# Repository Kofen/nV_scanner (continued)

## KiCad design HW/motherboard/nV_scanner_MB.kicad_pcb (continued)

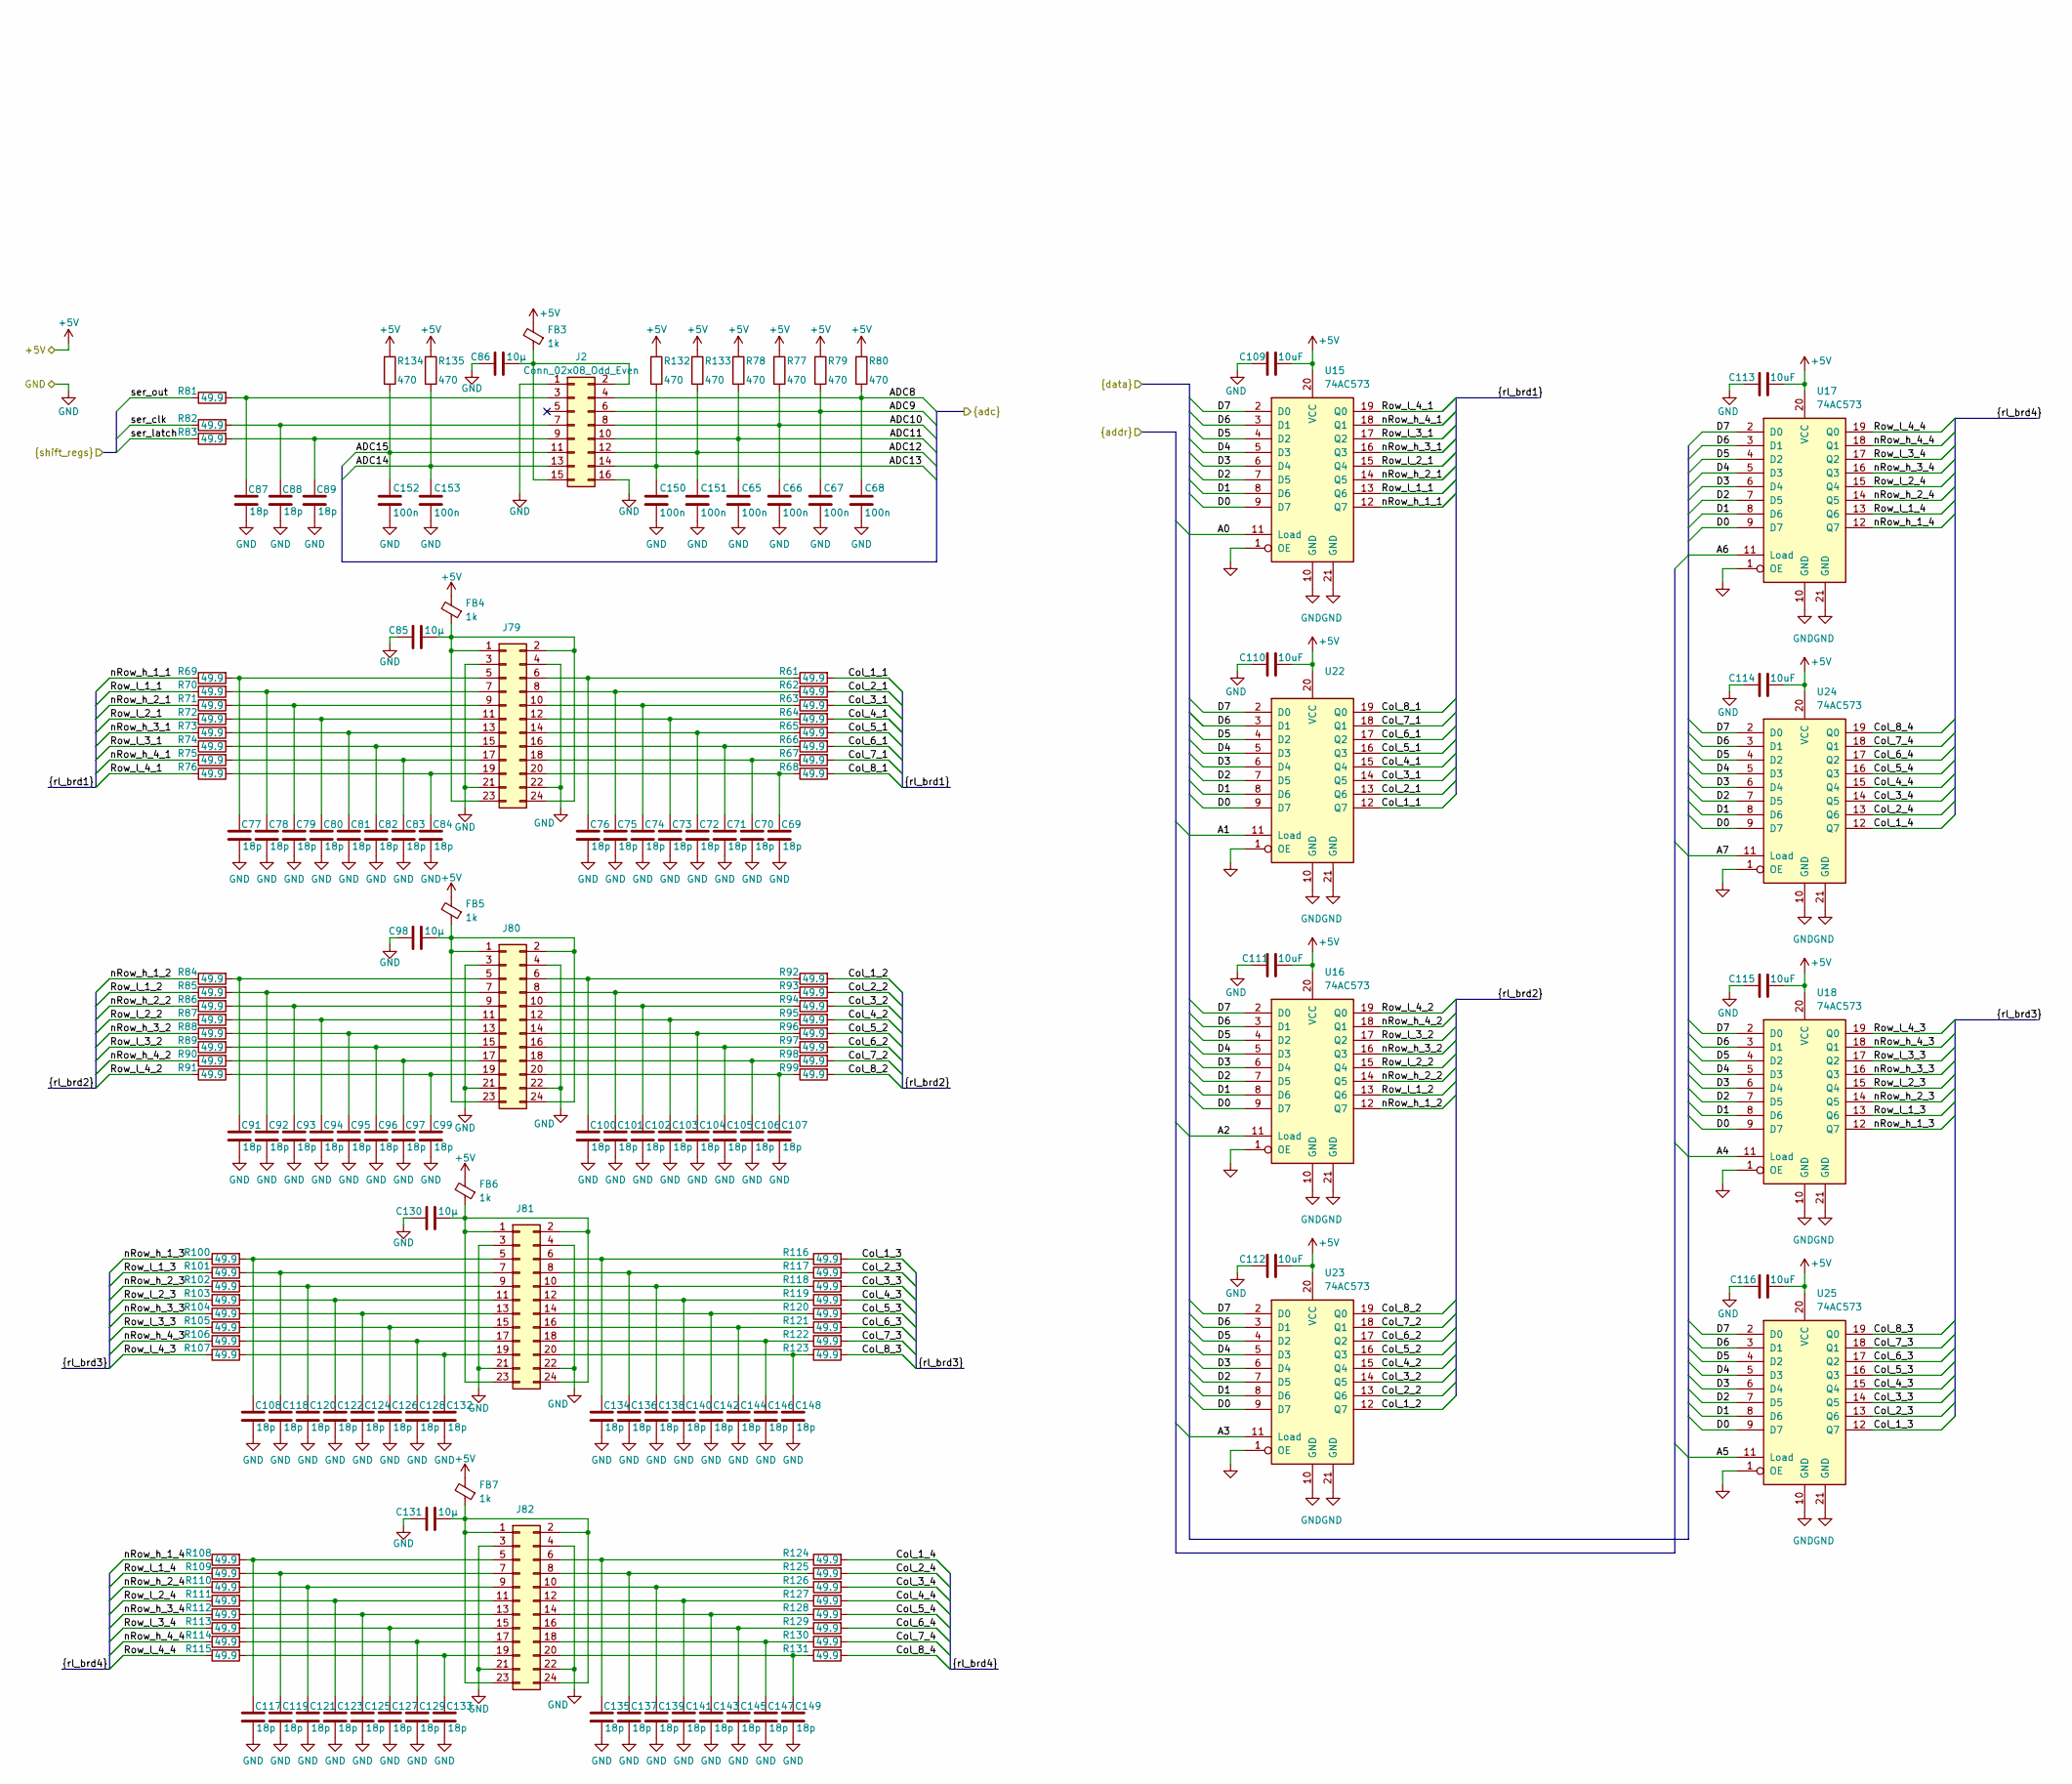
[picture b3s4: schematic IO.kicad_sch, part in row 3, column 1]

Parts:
C65, C66, C67, C68, C150, C151, C152, C153: 100n; C_0402_1005Metric; JLCPCB C1525
C69, C70, C71, C72, C73, C74, C75, C76, C77, C78, C79, C80, C81, C82, C83, C84, C87, C88, C89, C91, C92, C93, C94, C95, C96, C97, C99, C100, C101, C102, C103, C104, C105, C106, C107, C108, C117, C118, C119, C120, C121, C122, C123, C124, C125, C126, C127, C128, C129, C132, C133, C134, C135, C136, C137, C138, C139, C140, C141, C142, C143, C144, C145, C146, C147, C148, C149: 18p; C_0402_1005Metric; JLCPCB C1549
C85, C86, C98, C130, C131: 10µ; C_0402_1005Metric; JLCPCB C15525
C109, C110, C111, C112, C113, C114, C115, C116: 10uF; C_0603_1608Metric
FB3, FB4, FB5, FB6, FB7: 1k; L_0805_2012Metric; JLCPCB C710395
J2: Conn_02x08_Odd_Even; PinHeader_2x08_P2.54mm_Vertical
J79, J80, J81, J82: Conn_02x12_Odd_Even; PinHeader_2x12_P2.54mm_Vertical
R61, R62, R63, R64, R65, R66, R67, R68, R69, R70, R71, R72, R73, R74, R75, R76, R81, R82, R83, R84, R85, R86, R87, R88, R89, R90, R91, R92, R93, R94, R95, R96, R97, R98, R99, R100, R101, R102, R103, R104, R105, R106, R107, R108, R109, R110, R111, R112, R113, R114, R115, R116, R117, R118, R119, R120, R121, R122, R123, R124, R125, R126, R127, R128, R129, R130, R131: 49.9; R_0402_1005Metric
R77, R78, R79, R80, R132, R133, R134, R135: 470; R_0603_1608Metric
U15, U16, U17, U18, U22, U23, U24, U25: 74AC573; DHVQFN-20-1EP_2.5x4.5mm_P0.5mm_EP1x3mm

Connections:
+5V: C109.2, C110.2, C111.2, C112.2, C113.2, C114.2, C115.2, C116.2, FB3.2, FB4.2, FB5.2, FB6.2, FB7.2, R77.2, R78.2, R79.2, R80.2, R132.2, R133.2, R134.2, R135.2, U15.20 (VCC), U16.20 (VCC), U17.20 (VCC), U18.20 (VCC), U22.20 (VCC), U23.20 (VCC), U24.20 (VCC), U25.20 (VCC); also elsewhere on the board
/IO/A0: U15.11 (Load); also elsewhere on the board
/IO/A1: U22.11 (Load); also elsewhere on the board
/IO/A2: U16.11 (Load); also elsewhere on the board
/IO/A3: U23.11 (Load); also elsewhere on the board
/IO/A4: U18.11 (Load); also elsewhere on the board
/IO/A5: U25.11 (Load); also elsewhere on the board
/IO/A6: U17.11 (Load); also elsewhere on the board
/IO/A7: U24.11 (Load); also elsewhere on the board
/IO/ADC8: C68.2, J2.4, R80.1; also elsewhere on the board
/IO/ADC9: C67.2, J2.6, R79.1; also elsewhere on the board
/IO/ADC10: C66.2, J2.8, R77.1; also elsewhere on the board
/IO/ADC11: C65.2, J2.10, R78.1; also elsewhere on the board
/IO/ADC12: C151.2, J2.12, R133.1; also elsewhere on the board
/IO/ADC13: C150.2, J2.14, R132.1; also elsewhere on the board
/IO/ADC14: C153.2, J2.13, R135.1; also elsewhere on the board
/IO/ADC15: C152.2, J2.11, R134.1; also elsewhere on the board
/IO/Col_1_1: R61.2, U22.12 (Q7)
/IO/Col_1_2: R92.2, U23.12 (Q7)
/IO/Col_1_3: R116.2, U25.12 (Q7)
/IO/Col_1_4: R124.2, U24.12 (Q7)
/IO/Col_2_1: R62.2, U22.13 (Q6)
/IO/Col_2_2: R93.2, U23.13 (Q6)
/IO/Col_2_3: R117.2, U25.13 (Q6)
/IO/Col_2_4: R125.2, U24.13 (Q6)
/IO/Col_3_1: R63.2, U22.14 (Q5)
/IO/Col_3_2: R94.2, U23.14 (Q5)
/IO/Col_3_3: R118.2, U25.14 (Q5)
/IO/Col_3_4: R126.2, U24.14 (Q5)
/IO/Col_4_1: R64.2, U22.15 (Q4)
/IO/Col_4_2: R95.2, U23.15 (Q4)
/IO/Col_4_3: R119.2, U25.15 (Q4)
/IO/Col_4_4: R127.2, U24.15 (Q4)
/IO/Col_5_1: R65.2, U22.16 (Q3)
/IO/Col_5_2: R96.2, U23.16 (Q3)
/IO/Col_5_3: R120.2, U25.16 (Q3)
/IO/Col_5_4: R128.2, U24.16 (Q3)
/IO/Col_6_1: R66.2, U22.17 (Q2)
/IO/Col_6_2: R97.2, U23.17 (Q2)
/IO/Col_6_3: R121.2, U25.17 (Q2)
/IO/Col_6_4: R129.2, U24.17 (Q2)
/IO/Col_7_1: R67.2, U22.18 (Q1)
/IO/Col_7_2: R98.2, U23.18 (Q1)
/IO/Col_7_3: R122.2, U25.18 (Q1)
/IO/Col_7_4: R130.2, U24.18 (Q1)
/IO/Col_8_1: R68.2, U22.19 (Q0)
/IO/Col_8_2: R99.2, U23.19 (Q0)
/IO/Col_8_3: R123.2, U25.19 (Q0)
/IO/Col_8_4: R131.2, U24.19 (Q0)
/IO/D0: U15.9 (D7), U16.9 (D7), U17.9 (D7), U18.9 (D7), U22.9 (D7), U23.9 (D7), U24.9 (D7), U25.9 (D7); also elsewhere on the board
/IO/D1: U15.8 (D6), U16.8 (D6), U17.8 (D6), U18.8 (D6), U22.8 (D6), U23.8 (D6), U24.8 (D6), U25.8 (D6); also elsewhere on the board
/IO/D2: U15.7 (D5), U16.7 (D5), U17.7 (D5), U18.7 (D5), U22.7 (D5), U23.7 (D5), U24.7 (D5), U25.7 (D5); also elsewhere on the board
/IO/D3: U15.6 (D4), U16.6 (D4), U17.6 (D4), U18.6 (D4), U22.6 (D4), U23.6 (D4), U24.6 (D4), U25.6 (D4); also elsewhere on the board
/IO/D4: U15.5 (D3), U16.5 (D3), U17.5 (D3), U18.5 (D3), U22.5 (D3), U23.5 (D3), U24.5 (D3), U25.5 (D3); also elsewhere on the board
/IO/D5: U15.4 (D2), U16.4 (D2), U17.4 (D2), U18.4 (D2), U22.4 (D2), U23.4 (D2), U24.4 (D2), U25.4 (D2); also elsewhere on the board
/IO/D6: U15.3 (D1), U16.3 (D1), U17.3 (D1), U18.3 (D1), U22.3 (D1), U23.3 (D1), U24.3 (D1), U25.3 (D1); also elsewhere on the board
/IO/D7: U15.2 (D0), U16.2 (D0), U17.2 (D0), U18.2 (D0), U22.2 (D0), U23.2 (D0), U24.2 (D0), U25.2 (D0); also elsewhere on the board
/IO/Row_l_1_1: R70.1, U15.13 (Q6)
/IO/Row_l_1_2: R85.1, U16.13 (Q6)
/IO/Row_l_1_3: R101.1, U18.13 (Q6)
/IO/Row_l_1_4: R109.1, U17.13 (Q6)
/IO/Row_l_2_1: R72.1, U15.15 (Q4)
/IO/Row_l_2_2: R87.1, U16.15 (Q4)
/IO/Row_l_2_3: R103.1, U18.15 (Q4)
/IO/Row_l_2_4: R111.1, U17.15 (Q4)
/IO/Row_l_3_1: R74.1, U15.17 (Q2)
/IO/Row_l_3_2: R89.1, U16.17 (Q2)
/IO/Row_l_3_3: R105.1, U18.17 (Q2)
/IO/Row_l_3_4: R113.1, U17.17 (Q2)
/IO/Row_l_4_1: R76.1, U15.19 (Q0)
/IO/Row_l_4_2: R91.1, U16.19 (Q0)
/IO/Row_l_4_3: R107.1, U18.19 (Q0)
/IO/Row_l_4_4: R115.1, U17.19 (Q0)
/IO/nRow_h_1_1: R69.1, U15.12 (Q7)
/IO/nRow_h_1_2: R84.1, U16.12 (Q7)
/IO/nRow_h_1_3: R100.1, U18.12 (Q7)
/IO/nRow_h_1_4: R108.1, U17.12 (Q7)
/IO/nRow_h_2_1: R71.1, U15.14 (Q5)
/IO/nRow_h_2_2: R86.1, U16.14 (Q5)
/IO/nRow_h_2_3: R102.1, U18.14 (Q5)
/IO/nRow_h_2_4: R110.1, U17.14 (Q5)
/IO/nRow_h_3_1: R73.1, U15.16 (Q3)
/IO/nRow_h_3_2: R88.1, U16.16 (Q3)
/IO/nRow_h_3_3: R104.1, U18.16 (Q3)
/IO/nRow_h_3_4: R112.1, U17.16 (Q3)
/IO/nRow_h_4_1: R75.1, U15.18 (Q1)
/IO/nRow_h_4_2: R90.1, U16.18 (Q1)
/IO/nRow_h_4_3: R106.1, U18.18 (Q1)
/IO/nRow_h_4_4: R114.1, U17.18 (Q1)
/IO/ser_clk: R82.1; also elsewhere on the board
/IO/ser_latch: R83.1; also elsewhere on the board
/IO/ser_out: R81.1; also elsewhere on the board
GND: C65.1, C66.1, C67.1, C68.1, C69.2, C70.2, C71.2, C72.2, C73.2, C74.2, C75.2, C76.2, C77.2, C78.2, C79.2, C80.2, C81.2, C82.2, C83.2, C84.2, C85.2, C86.2, C87.2, C88.2, C89.2, C91.2, C92.2, C93.2, C94.2, C95.2, C96.2, C97.2, C98.2, C99.2, C100.2, C101.2, C102.2, C103.2, C104.2, C105.2, C106.2, C107.2, C108.2, C109.1, C110.1, C111.1, C112.1, C113.1, C114.1, C115.1, C116.1, C117.2, C118.2, C119.2, C120.2, C121.2, C122.2, C123.2, C124.2, C125.2, C126.2, C127.2, C128.2, C129.2, C130.2, C131.2, C132.2, C133.2, C134.2, C135.2, C136.2, C137.2, C138.2, C139.2, C140.2, C141.2, C142.2, C143.2, C144.2, C145.2, C146.2, C147.2, C148.2, C149.2, C150.1, C151.1, C152.1, C153.1, J2.1, J2.16, J79.3, J79.4, J79.21, J79.22, J80.3, J80.4, J80.21, J80.22, J81.3, J81.4, J81.21, J81.22, J82.3, J82.4, J82.21, J82.22, U15.1 (OE), U15.10 (GND), U15.21 (GND), U16.1 (OE), U16.10 (GND), U16.21 (GND), U17.1 (OE), U17.10 (GND), U17.21 (GND), U18.1 (OE), U18.10 (GND), U18.21 (GND), U22.1 (OE), U22.10 (GND), U22.21 (GND), U23.1 (OE), U23.10 (GND), U23.21 (GND), U24.1 (OE), U24.10 (GND), U24.21 (GND), U25.1 (OE), U25.10 (GND), U25.21 (GND); also elsewhere on the board
unnamed: C87.1, J2.3, R81.2
unnamed: C88.1, J2.7, R82.2
unnamed: C89.1, J2.9, R83.2
unnamed: C86.1, FB3.1, J2.2, J2.15
unnamed: C85.1, FB4.1, J79.1, J79.2, J79.23, J79.24
unnamed: C77.1, J79.5, R69.2
unnamed: C76.1, J79.6, R61.1
unnamed: C78.1, J79.7, R70.2
unnamed: C75.1, J79.8, R62.1
unnamed: C79.1, J79.9, R71.2
unnamed: C74.1, J79.10, R63.1
unnamed: C80.1, J79.11, R72.2
unnamed: C73.1, J79.12, R64.1
unnamed: C81.1, J79.13, R73.2
unnamed: C72.1, J79.14, R65.1
unnamed: C82.1, J79.15, R74.2
unnamed: C71.1, J79.16, R66.1
unnamed: C83.1, J79.17, R75.2
unnamed: C70.1, J79.18, R67.1
unnamed: C84.1, J79.19, R76.2
unnamed: C69.1, J79.20, R68.1
unnamed: C98.1, FB5.1, J80.1, J80.2, J80.23, J80.24
unnamed: C91.1, J80.5, R84.2
unnamed: C100.1, J80.6, R92.1
unnamed: C92.1, J80.7, R85.2
unnamed: C101.1, J80.8, R93.1
unnamed: C93.1, J80.9, R86.2
unnamed: C102.1, J80.10, R94.1
unnamed: C94.1, J80.11, R87.2
unnamed: C103.1, J80.12, R95.1
unnamed: C95.1, J80.13, R88.2
unnamed: C104.1, J80.14, R96.1
unnamed: C96.1, J80.15, R89.2
unnamed: C105.1, J80.16, R97.1
unnamed: C97.1, J80.17, R90.2
unnamed: C106.1, J80.18, R98.1
unnamed: C99.1, J80.19, R91.2
unnamed: C107.1, J80.20, R99.1
unnamed: C130.1, FB6.1, J81.1, J81.2, J81.23, J81.24
unnamed: C108.1, J81.5, R100.2
unnamed: C134.1, J81.6, R116.1
unnamed: C118.1, J81.7, R101.2
unnamed: C136.1, J81.8, R117.1
unnamed: C120.1, J81.9, R102.2
unnamed: C138.1, J81.10, R118.1
unnamed: C122.1, J81.11, R103.2
unnamed: C140.1, J81.12, R119.1
unnamed: C124.1, J81.13, R104.2
unnamed: C142.1, J81.14, R120.1
unnamed: C126.1, J81.15, R105.2
unnamed: C144.1, J81.16, R121.1
unnamed: C128.1, J81.17, R106.2
unnamed: C146.1, J81.18, R122.1
unnamed: C132.1, J81.19, R107.2
unnamed: C148.1, J81.20, R123.1
unnamed: C131.1, FB7.1, J82.1, J82.2, J82.23, J82.24
unnamed: C117.1, J82.5, R108.2
unnamed: C135.1, J82.6, R124.1
unnamed: C119.1, J82.7, R109.2
unnamed: C137.1, J82.8, R125.1
unnamed: C121.1, J82.9, R110.2
unnamed: C139.1, J82.10, R126.1
unnamed: C123.1, J82.11, R111.2
unnamed: C141.1, J82.12, R127.1
unnamed: C125.1, J82.13, R112.2
unnamed: C143.1, J82.14, R128.1
unnamed: C127.1, J82.15, R113.2
unnamed: C145.1, J82.16, R129.1
unnamed: C129.1, J82.17, R114.2
unnamed: C147.1, J82.18, R130.1
unnamed: C133.1, J82.19, R115.2
unnamed: C149.1, J82.20, R131.1

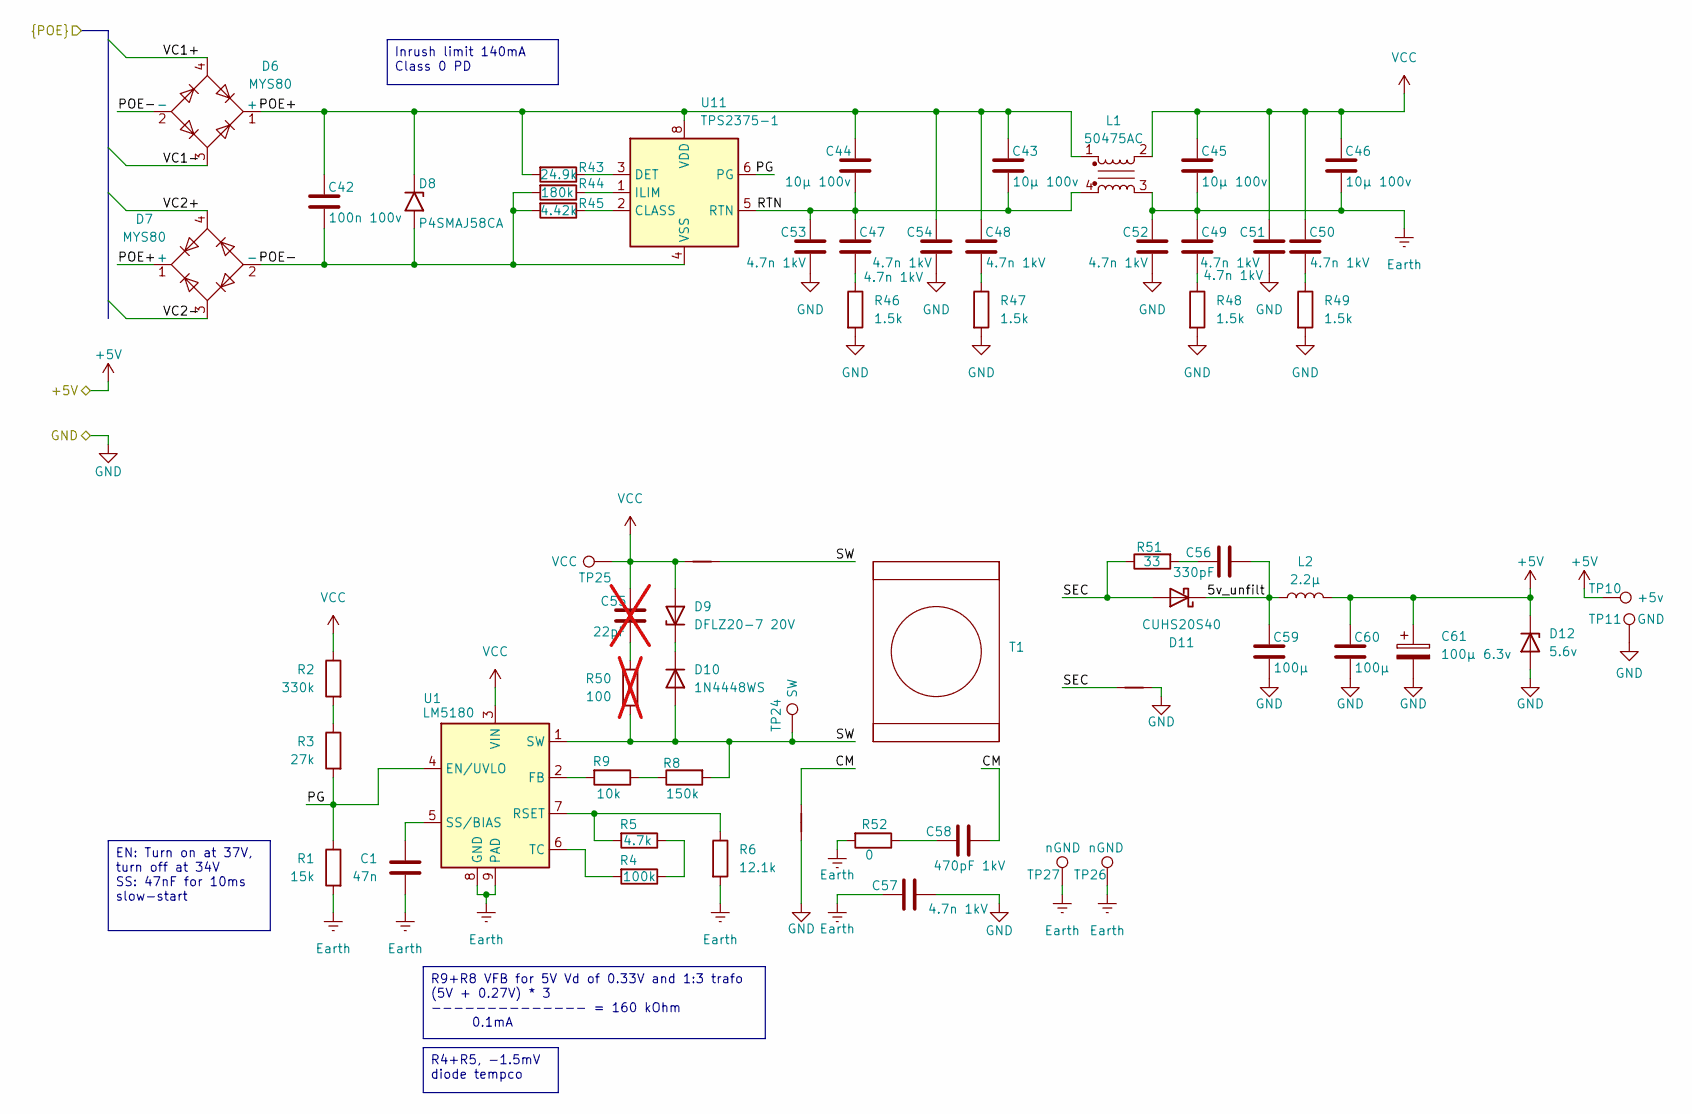
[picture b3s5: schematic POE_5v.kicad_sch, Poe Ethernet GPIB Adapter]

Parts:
C1: 47n; C_0402_1005Metric; JLCPCB C82219
C42: 100n 100v; C_0603_1608Metric; JLCPCB C15725
C43, C44, C45, C46: 10µ 100v; C_1210_3225Metric; JLCPCB C5156756
C47, C48, C49, C50, C51, C52, C53, C54, C57: 4.7n 1kV; C_0805_2012Metric; JLCPCB C565695
C55: 22pF; C_0603_1608Metric; not fitted
C56: 330pF; C_0603_1608Metric; JLCPCB C458879
C58: 470pF 1kV; C_0805_2012Metric; JLCPCB C20416464
C59, C60: 100µ; C_1206_3216Metric; JLCPCB CL31A107MQHNNNE
C61: 100µ 6.3v; CP_Elec_5x5.3; JLCPCB C5530352
D6, D7: MYS80; Diode_Bridge_Diotec_MicroDil_3.0x3.0x1.8mm; JLCPCB C3589669
D8: P4SMAJ58CA; D_SMA; JLCPCB C268635
D9: DFLZ20-7 20V; D_PowerDI-123; JLCPCB C177024
D10: 1N4448WS; D_SOD-323; JLCPCB C8602
D11: CUHS20S40; D_TUMD2; JLCPCB C3758140
D12: 5.6v; D_SOD-123F; JLCPCB C2119
L1: 50475AC; muRata_5000A
L2: 2.2µ; L_Taiyo-Yuden_NR-50xx
NT1, NT2: NetTie_2; NetTie-2_SMD_Pad0.5mm
NT3: NetTie_2; NetTie-2_SMD_Pad0.8mm
R1: 15k; R_0402_1005Metric
R2: 330k; R_0805_2012Metric
R3: 27k; R_0402_1005Metric
R4: 100k; R_0402_1005Metric
R5: 4.7k; R_0402_1005Metric
R6: 12.1k; R_0402_1005Metric
R8: 150k; R_0805_2012Metric
R9: 10k; R_0402_1005Metric
R43: 24.9k; R_0402_1005Metric
R44: 180k; R_0402_1005Metric
R45: 4.42k; R_0402_1005Metric
R46, R47, R48, R49: 1.5k; R_0603_1608Metric
R50: 100; R_0603_1608Metric; not fitted
R51: 33; R_0603_1608Metric
R52: 0; R_0603_1608Metric
T1: ER14_planar_4_to_1_48v_in_5v_out_5w
TP10: +5v; TestPoint_Pad_D1.0mm
TP11: GND; TestPoint_Pad_D1.0mm
TP24: SW; TestPoint_Pad_D1.0mm
TP25: VCC; TestPoint_Pad_D1.0mm
TP26, TP27: nGND; TestPoint_Pad_D1.0mm
U1: LM5180; WSON-8-1EP_4x4mm_P0.8mm_EP1.98x3mm; JLCPCB C2868878
U11: TPS2375-1; TSSOP-8_4.4x3mm_P0.65mm; JLCPCB C2859774

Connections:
+5V: C60.1, C61.1, D12.1 (K), L2.2, TP10.1; also elsewhere on the board
/Ethernet_interface/VC1+: D6.4; also elsewhere on the board
/Ethernet_interface/VC1-: D6.3; also elsewhere on the board
/Ethernet_interface/VC2+: D7.4; also elsewhere on the board
/Ethernet_interface/VC2-: D7.3; also elsewhere on the board
/POE_5v/5v_unfilt: C56.2, C59.1, D11.1 (K), L2.1
/POE_5v/CM: C58.1, NT2.2
/POE_5v/PG: R1.1, R3.2, U1.4 (EN/UVLO), U11.6 (PG)
/POE_5v/POE+: C42.1, C43.1, C44.1, C48.1, C54.1, D6.1 (+), D7.1 (+), D8.1 (A1), L1.1, R43.2, U11.8 (VDD)
/POE_5v/POE-: C42.2, D6.2 (-), D7.2 (-), D8.2 (A2), R44.2, R45.2, U11.4 (VSS)
/POE_5v/RTN: C43.2, C44.2, C47.1, C53.1, L1.4, U11.5 (RTN)
/POE_5v/SEC: D11.2 (A), NT3.1, R51.1
/POE_5v/SW: D10.2 (A), NT1.2, R8.2, R50.2, TP24.1, U1.1 (SW)
Earth: C1.2, C45.2, C46.2, C49.1, C52.1, C57.2, L1.3, R1.2, R6.2, R52.2, TP26.1, TP27.1, U1.8 (GND), U1.9 (PAD)
GND: C51.2, C52.2, C53.2, C54.2, C57.1, C59.2, C60.2, C61.2, D12.2 (A), NT2.1, NT3.2, R46.2, R47.2, R48.2, R49.2, TP11.1; also elsewhere on the board
unnamed: C47.2, R46.1
unnamed: C48.2, R47.1
unnamed: C49.2, R48.1
unnamed: C50.2, R49.1
unnamed: C55.2, R50.1
unnamed: C56.1, R51.2
unnamed: C58.2, R52.1
unnamed: D9.1 (K), D10.1 (K)
unnamed: R2.2, R3.1
unnamed: R4.1, R5.1
unnamed: R8.1, R9.1
unnamed: R9.2, U1.2 (FB)
unnamed: R5.2, R6.1, U1.7 (RSET)
unnamed: C1.1, U1.5 (SS/BIAS)
unnamed: R4.2, U1.6 (TC)
unnamed: R45.1, U11.2 (CLASS)
unnamed: R43.1, U11.3 (DET)
unnamed: R44.1, U11.1 (ILIM)
VCC: C45.1, C46.1, C50.1, C51.1, C55.1, D9.2 (A), L1.2, NT1.1, R2.1, TP25.1, U1.3 (VIN)

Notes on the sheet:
R9+R8 VFB for 5V Vd of 0.33V and 1:3 trafo (5V + 0.27V) * 3 -------------- = 160 kOhm 0.1mA
R4+R5, -1.5mV diode tempco
EN: Turn on at 37V, turn off at 34V SS: 47nF for 10ms slow-start
Inrush limit 140mA Class 0 PD

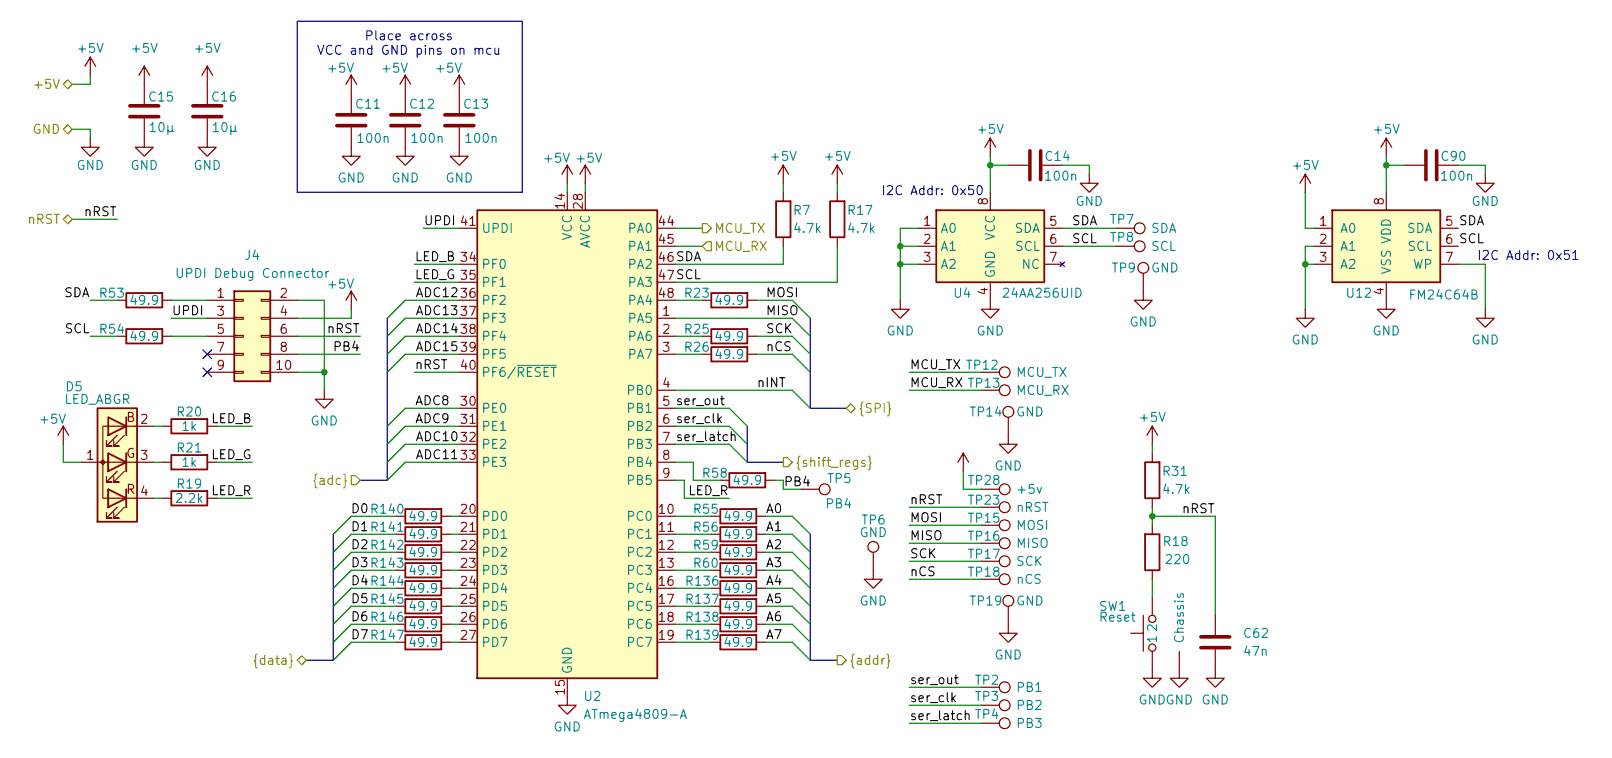
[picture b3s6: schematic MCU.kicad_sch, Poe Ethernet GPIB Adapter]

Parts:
C11, C12, C13, C14, C90: 100n; C_0402_1005Metric; JLCPCB C1525
C15, C16: 10µ; C_0402_1005Metric; JLCPCB C15525
C62: 47n; C_0402_1005Metric; JLCPCB C82219
D5: LED_ABGR; LED_RGB_Everlight_EASV3015RGBA0_Horizontal; JLCPCB C5365900
J4: UPDI Debug Connector; PinHeader_2x05_P1.27mm_Vertical
R7, R17, R31: 4.7k; R_0402_1005Metric
R18: 220; R_0402_1005Metric
R19: 2.2k; R_0402_1005Metric
R20, R21: 1k; R_0402_1005Metric
R23, R25, R26, R53, R54, R55, R56, R58, R59, R60, R136, R137, R138, R139, R140, R141, R142, R143, R144, R145, R146, R147: 49.9; R_0402_1005Metric
SW1: Reset; SW_Tactile_SKHH_Angled
TP2: PB1; TestPoint_Pad_D1.0mm
TP3: PB2; TestPoint_Pad_D1.0mm
TP4: PB3; TestPoint_Pad_D1.0mm
TP5: PB4; TestPoint_Pad_D1.0mm
TP6, TP9, TP14, TP19: GND; TestPoint_Pad_D1.0mm
TP7: SDA; TestPoint_Pad_D1.0mm
TP8: SCL; TestPoint_Pad_D1.0mm
TP12: MCU_TX; TestPoint_Pad_D1.0mm
TP13: MCU_RX; TestPoint_Pad_D1.0mm
TP15: MOSI; TestPoint_Pad_D1.0mm
TP16: MISO; TestPoint_Pad_D1.0mm
TP17: SCK; TestPoint_Pad_D1.0mm
TP18: nCS; TestPoint_Pad_D1.0mm
TP23: nRST; TestPoint_Pad_D1.0mm
TP28: +5v; TestPoint_Pad_D1.0mm
U2: ATmega4809-A; TQFP-48_7x7mm_P0.5mm; JLCPCB C1340041
U4: 24AA256UID; SOIC-8_3.9x4.9mm_P1.27mm; JLCPCB C1349800
U12: FM24C64B; SOIC-8_3.9x4.9mm_P1.27mm

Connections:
+5V: C11.2, C12.2, C13.2, C14.1, C15.1, C16.1, C90.1, D5.1 (A), J4.4, R7.2, R17.2, R31.2, TP28.1, U2.14 (VCC), U2.28 (AVCC), U2.42 (VCC), U4.8 (VCC), U12.1 (A0), U12.8 (VDD); also elsewhere on the board
/Ethernet_interface/MISO: TP16.1, U2.1 (PA5); also elsewhere on the board
/Ethernet_interface/MOSI: R23.2, TP15.1; also elsewhere on the board
/Ethernet_interface/SCK: R25.2, TP17.1; also elsewhere on the board
/Ethernet_interface/nCS: R26.2, TP18.1; also elsewhere on the board
/Ethernet_interface/nINT: U2.4 (PB0); also elsewhere on the board
/Ethernet_interface/nRST: C62.1, J4.6, R18.2, R31.1, TP23.1, U2.40 (PF6/~RESET); also elsewhere on the board
/IO/A0: R55.2; also elsewhere on the board
/IO/A1: R56.2; also elsewhere on the board
/IO/A2: R59.2; also elsewhere on the board
/IO/A3: R60.2; also elsewhere on the board
/IO/A4: R136.2; also elsewhere on the board
/IO/A5: R137.2; also elsewhere on the board
/IO/A6: R138.2; also elsewhere on the board
/IO/A7: R139.2; also elsewhere on the board
/IO/ADC8: U2.30 (PE0); also elsewhere on the board
/IO/ADC9: U2.31 (PE1); also elsewhere on the board
/IO/ADC10: U2.32 (PE2); also elsewhere on the board
/IO/ADC11: U2.33 (PE3); also elsewhere on the board
/IO/ADC12: U2.36 (PF2); also elsewhere on the board
/IO/ADC13: U2.37 (PF3); also elsewhere on the board
/IO/ADC14: U2.38 (PF4); also elsewhere on the board
/IO/ADC15: U2.39 (PF5); also elsewhere on the board
/IO/D0: R140.1; also elsewhere on the board
/IO/D1: R141.1; also elsewhere on the board
/IO/D2: R142.1; also elsewhere on the board
/IO/D3: R143.1; also elsewhere on the board
/IO/D4: R144.1; also elsewhere on the board
/IO/D5: R145.1; also elsewhere on the board
/IO/D6: R146.1; also elsewhere on the board
/IO/D7: R147.1; also elsewhere on the board
/IO/ser_clk: TP3.1, U2.6 (PB2); also elsewhere on the board
/IO/ser_latch: TP4.1, U2.7 (PB3); also elsewhere on the board
/IO/ser_out: TP2.1, U2.5 (PB1); also elsewhere on the board
/MCU/LED_B: R20.2, U2.34 (PF0)
/MCU/LED_G: R21.2, U2.35 (PF1)
/MCU/LED_R: R19.2, U2.9 (PB5)
/MCU/MCU_RX: TP13.1, U2.45 (PA1); also elsewhere on the board
/MCU/MCU_TX: TP12.1, U2.44 (PA0); also elsewhere on the board
/MCU/PB4: J4.8, R58.2, TP5.1
/MCU/SCL: R17.1, R54.1, TP8.1, U2.47 (PA3), U4.6 (SCL), U12.6 (SCL)
/MCU/SDA: R7.1, R53.1, TP7.1, U2.46 (PA2), U4.5 (SDA), U12.5 (SDA)
/MCU/UPDI: J4.3, U2.41 (UPDI)
GND: C11.1, C12.1, C13.1, C14.2, C15.2, C16.2, C62.2, C90.2, J4.2, J4.10, SW1.1, SW1.G (Chassis), TP6.1, TP9.1, TP14.1, TP19.1, U2.15 (GND), U2.29 (GND), U2.43 (GND), U4.1 (A0), U4.2 (A1), U4.3 (A2), U4.4 (GND), U12.2 (A1), U12.3 (A2), U12.4 (VSS), U12.7 (WP); also elsewhere on the board
unnamed: D5.2 (BK), R20.1
unnamed: D5.3 (GK), R21.1
unnamed: D5.4 (RK), R19.1
unnamed: J4.1, R53.2
unnamed: J4.5, R54.2
unnamed: R18.1, SW1.2
unnamed: R23.1, U2.48 (PA4)
unnamed: R25.1, U2.2 (PA6)
unnamed: R26.1, U2.3 (PA7)
unnamed: R58.1, U2.8 (PB4)
unnamed: R55.1, U2.10 (PC0)
unnamed: R56.1, U2.11 (PC1)
unnamed: R59.1, U2.12 (PC2)
unnamed: R60.1, U2.13 (PC3)
unnamed: R136.1, U2.16 (PC4)
unnamed: R137.1, U2.17 (PC5)
unnamed: R138.1, U2.18 (PC6)
unnamed: R139.1, U2.19 (PC7)
unnamed: R140.2, U2.20 (PD0)
unnamed: R141.2, U2.21 (PD1)
unnamed: R142.2, U2.22 (PD2)
unnamed: R143.2, U2.23 (PD3)
unnamed: R144.2, U2.24 (PD4)
unnamed: R145.2, U2.25 (PD5)
unnamed: R146.2, U2.26 (PD6)
unnamed: R147.2, U2.27 (PD7)

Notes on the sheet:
I2C Addr: 0x51
I2C Addr: 0x50
Place across VCC and GND pins on mcu

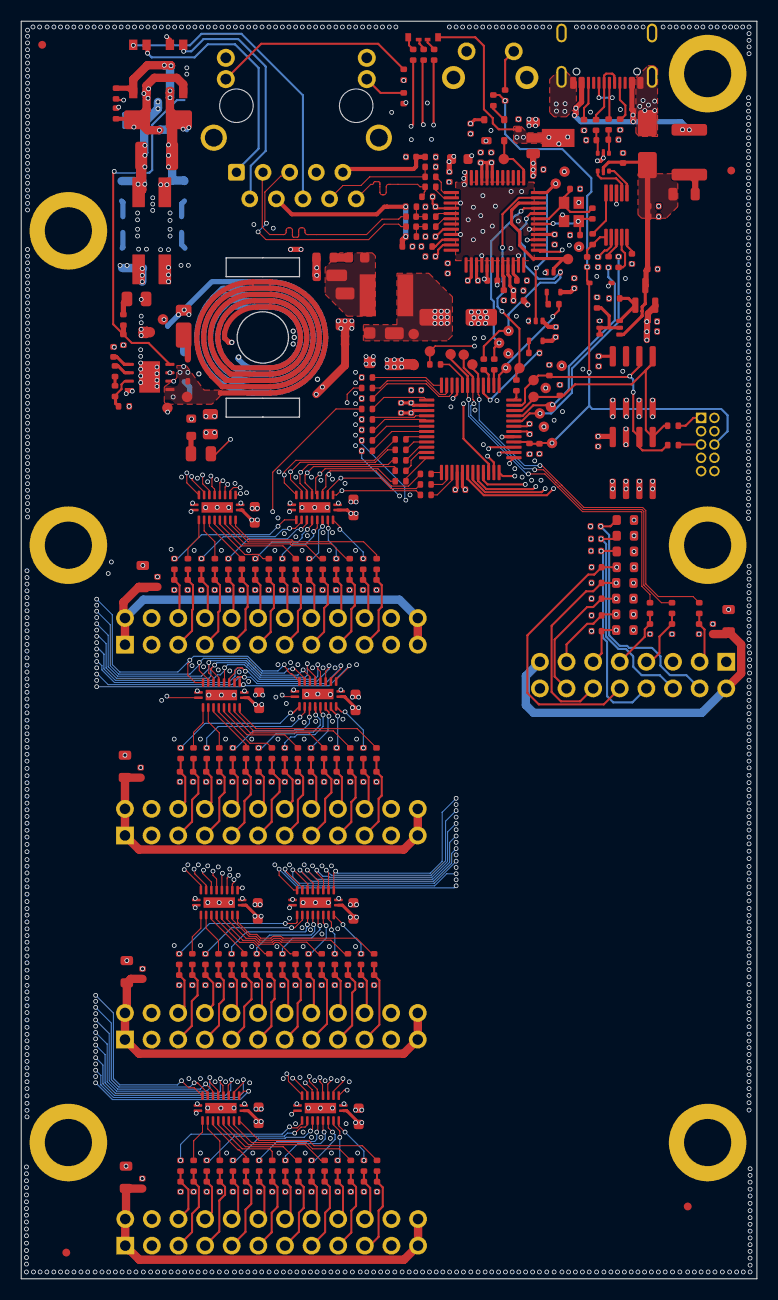
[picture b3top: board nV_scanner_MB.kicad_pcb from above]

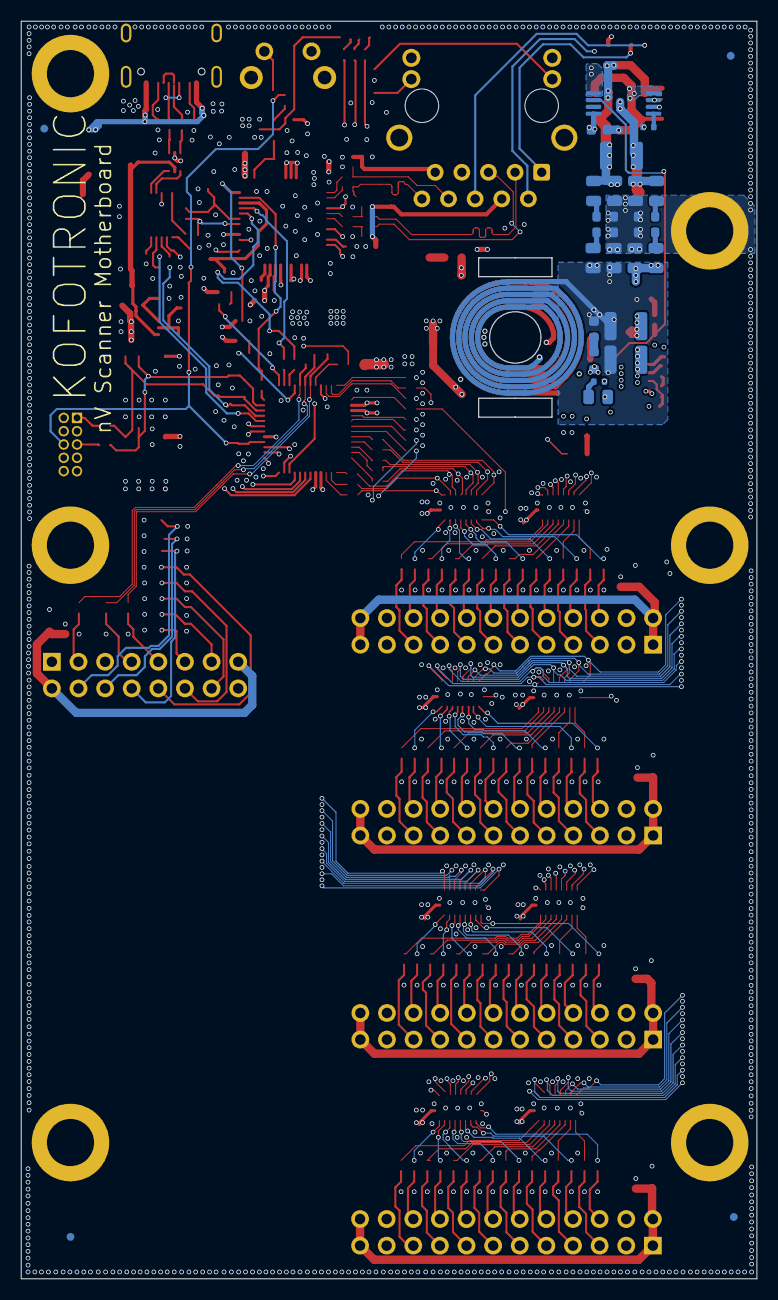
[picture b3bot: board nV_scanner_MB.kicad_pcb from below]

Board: 6 copper layers, 70.2 x 120.0 mm, 398 parts (27 on the bottom side), 285 nets.
